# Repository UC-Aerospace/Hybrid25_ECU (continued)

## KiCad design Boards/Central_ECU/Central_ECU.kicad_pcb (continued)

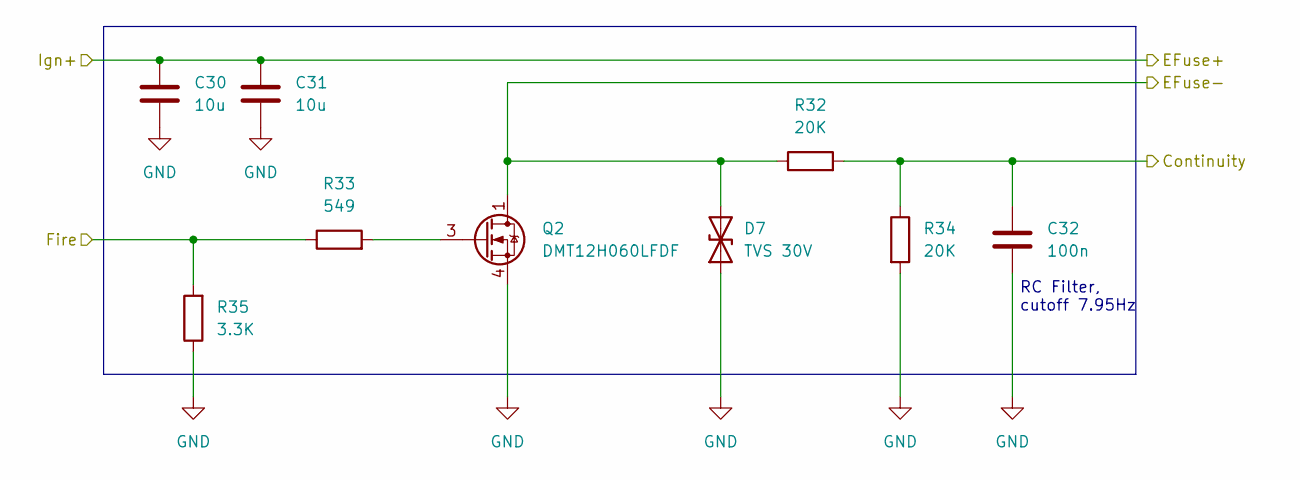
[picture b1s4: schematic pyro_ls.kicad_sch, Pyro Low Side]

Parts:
C30, C31: 10u; C_1206_3216Metric
C32: 100n; C_0603_1608Metric
D7: TVS 30V; D_SOD-882; MPN PESD1CANFD30L-QYL
Q2: DMT12H060LFDF; Diodes_UDFN2020-6_Type-F; MPN DMT12H060LFDF-7
R32, R34: 20K; R_0603_1608Metric
R33: 549; R_0603_1608Metric
R35: 3.3K; R_0603_1608Metric

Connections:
/Connectors/EMATCH_1+: C30.1, C31.1; also elsewhere on the board
/Connectors/EMATCH_2-: D7.2 (A2), Q2.1, Q2.2 (D), Q2.5 (D), Q2.6 (D), Q2.7 (D), R32.1; also elsewhere on the board
/EMATCH_2_FIRE: R33.1, R35.2; also elsewhere on the board
/Interlocked/Pyro Low Side1/Continuity: C32.1, R32.2, R34.1; also elsewhere on the board
GND: C30.2, C31.2, C32.2, D7.1 (A1), Q2.4, Q2.8 (S), R34.2, R35.1; also elsewhere on the board
unnamed: Q2.3, R33.2

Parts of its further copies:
C33, C34: 10u; C_1206_3216Metric
C35: 100n; C_0603_1608Metric
D15: TVS 30V; D_SOD-882; MPN PESD1CANFD30L-QYL
Q3: DMT12H060LFDF; Diodes_UDFN2020-6_Type-F; MPN DMT12H060LFDF-7
R36, R38: 20K; R_0603_1608Metric
R37: 549; R_0603_1608Metric
R39: 3.3K; R_0603_1608Metric

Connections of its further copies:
/Connectors/EMATCH_1+: C33.1, C34.1; also elsewhere on the board
/Connectors/EMATCH_1-: D15.2 (A2), Q3.1, Q3.2 (D), Q3.5 (D), Q3.6 (D), Q3.7 (D), R36.1; also elsewhere on the board
/EMATCH_1_FIRE: R37.1, R39.2; also elsewhere on the board
/Interlocked/Pyro Low Side/Continuity: C35.1, R36.2, R38.1; also elsewhere on the board
GND: C33.2, C34.2, C35.2, D15.1 (A1), Q3.4, Q3.8 (S), R38.2, R39.1; also elsewhere on the board
unnamed: Q3.3, R37.2

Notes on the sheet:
RC Filter, cutoff 7.95Hz

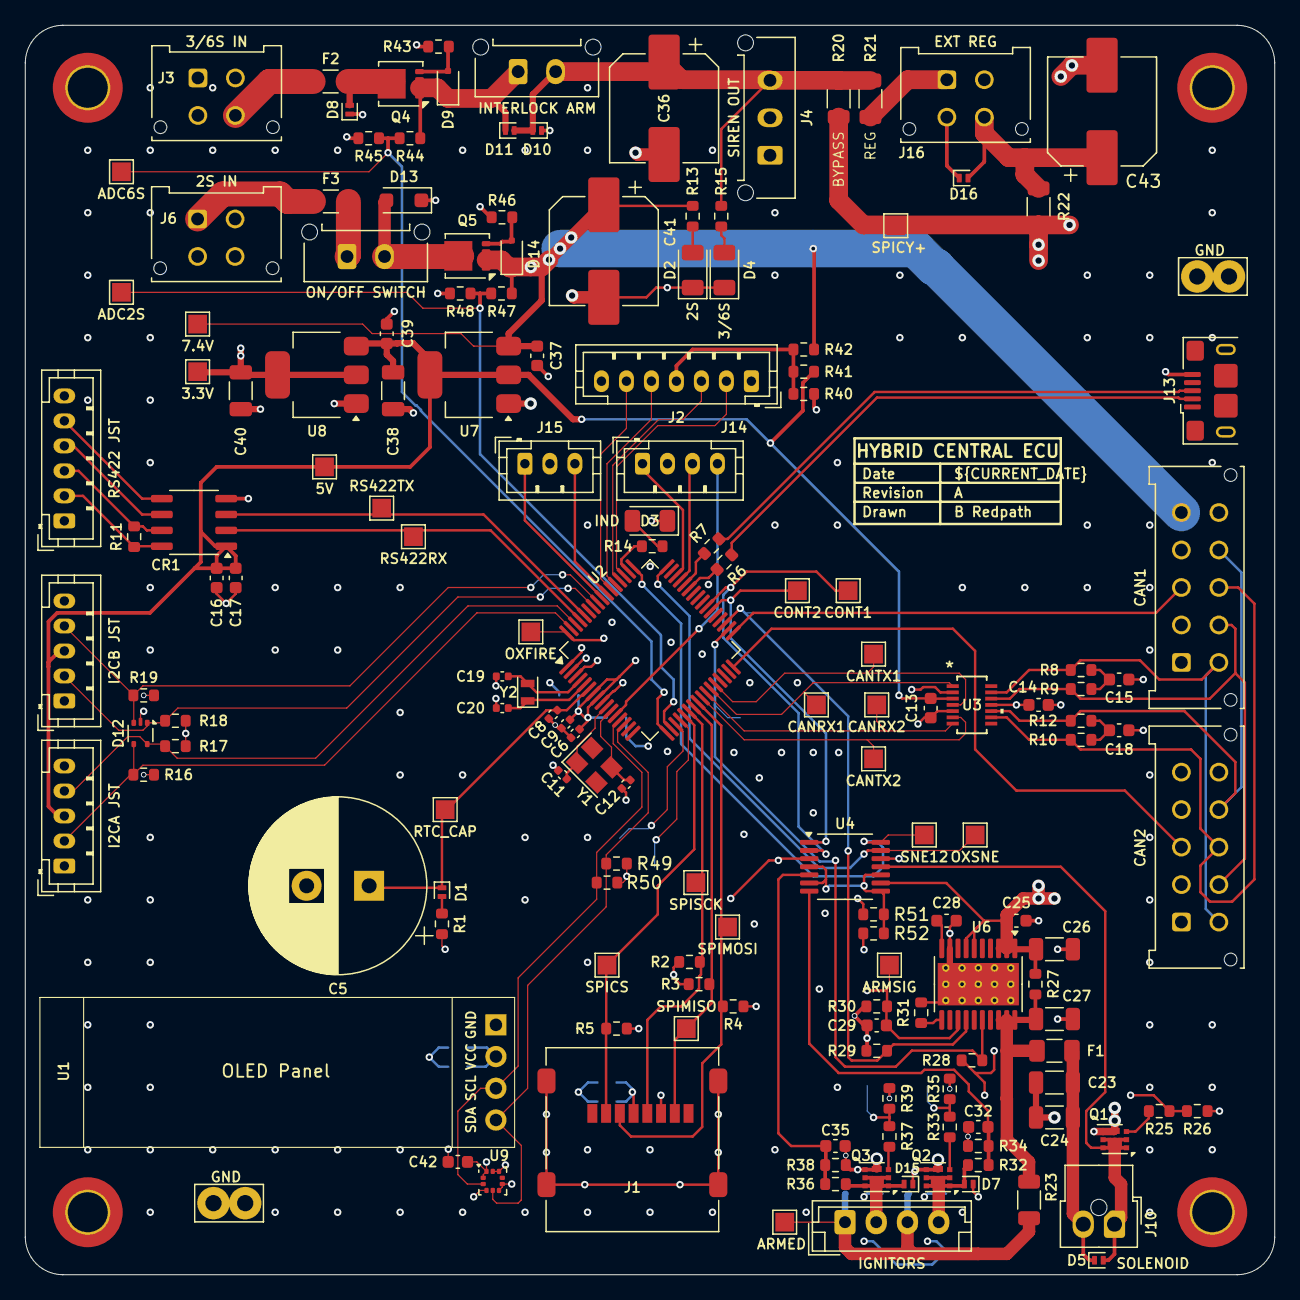
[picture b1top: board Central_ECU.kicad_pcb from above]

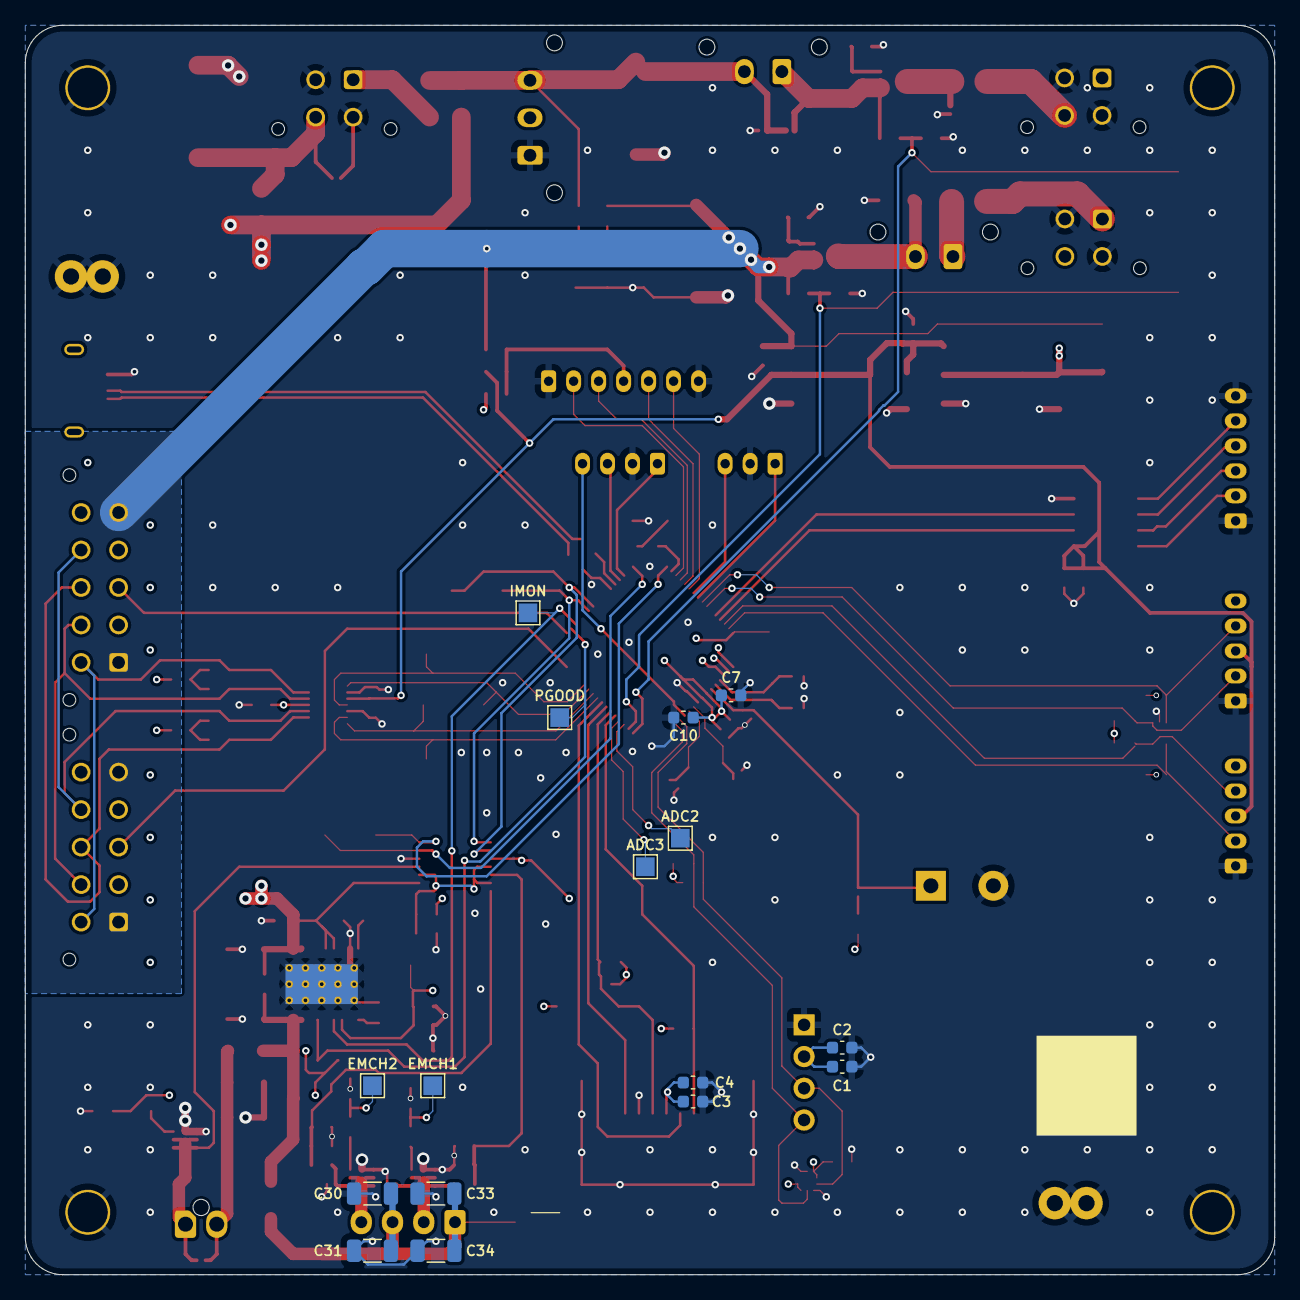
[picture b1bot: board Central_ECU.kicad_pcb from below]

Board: 4 copper layers, 100.0 x 100.0 mm, 180 parts (16 on the bottom side), 93 nets.

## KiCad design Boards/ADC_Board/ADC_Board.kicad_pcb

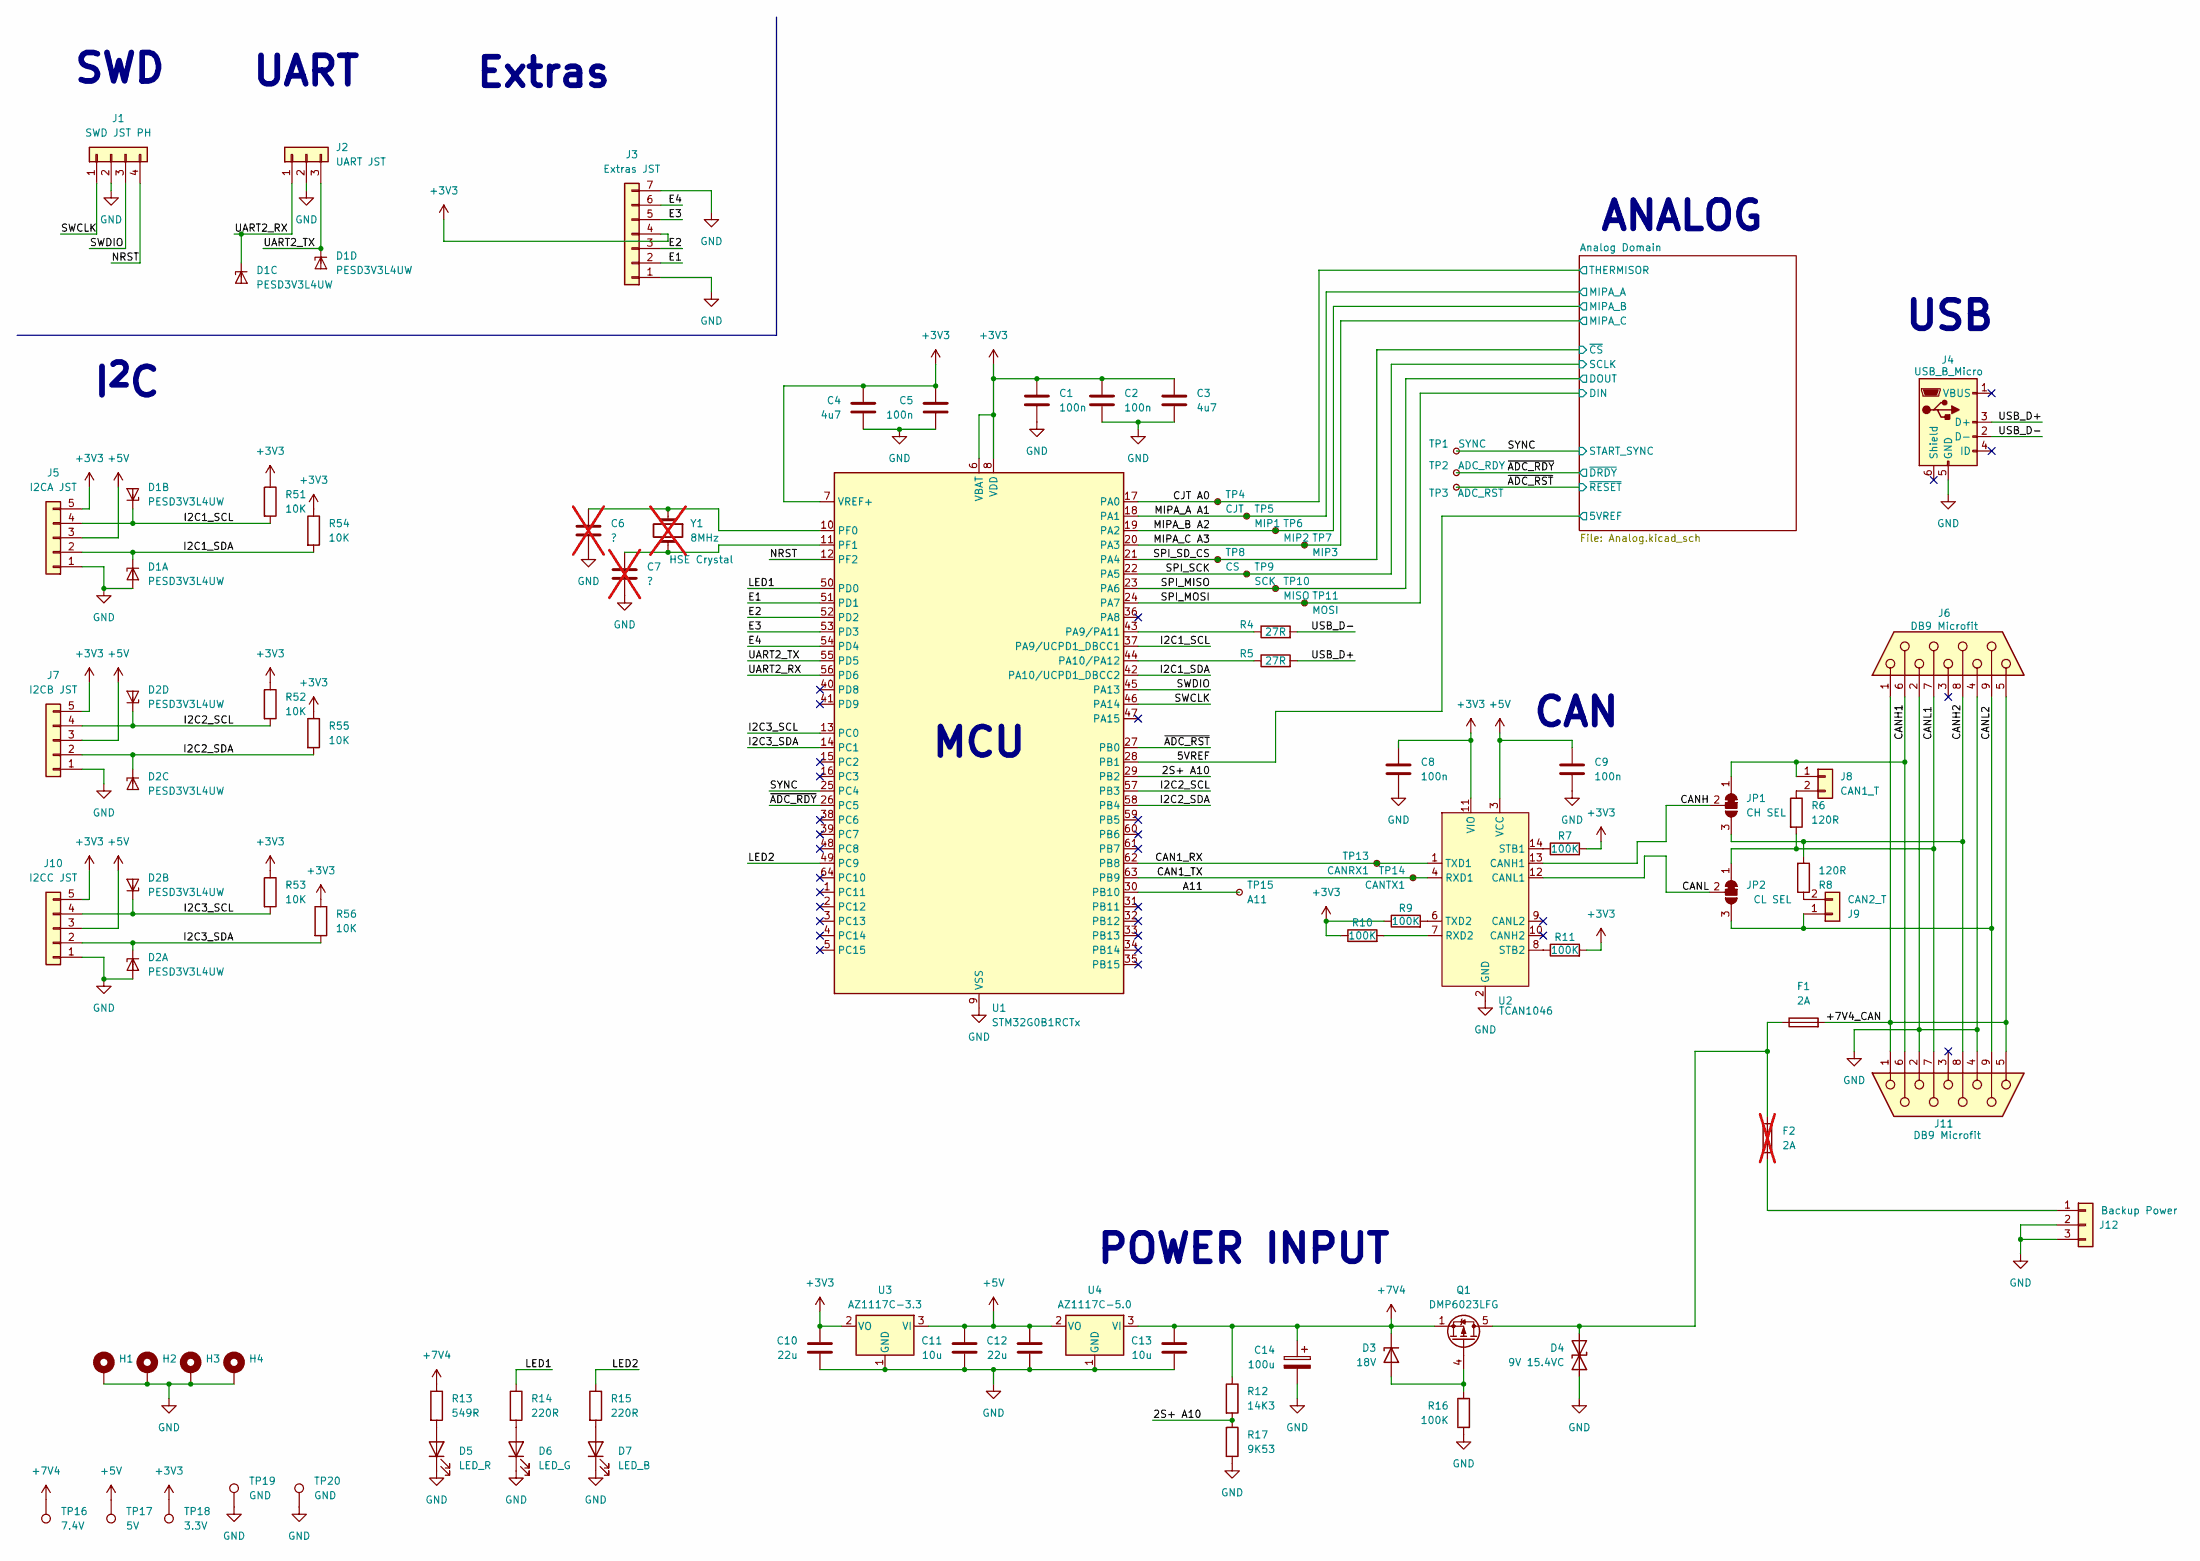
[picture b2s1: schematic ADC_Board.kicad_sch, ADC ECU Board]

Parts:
C1, C2, C5: 100n; C_0402_1005Metric
C3, C4: 4u7; C_0603_1608Metric
C6, C7: ?; C_0402_1005Metric; not fitted
C8, C9: 100n; C_0603_1608Metric
C10, C12: 22u; C_1206_3216Metric
C11, C13: 10u; C_0603_1608Metric
C14: 100u; CP_Elec_8x10.5; MPN A768KS107M1HLAE030
D1, D2: PESD3V3L4UW; SOT-665
D3: 18V; D_SOD-323F; MPN MM3Z18VB
D4: 9V 15.4VC; D_SOD-123F; MPN SMF9.0CA
D5: LED_R; LED_1206_3216Metric; MPN LTST-C150KRKT
D6: LED_G; LED_1206_3216Metric; MPN LTST-C150KGKT
D7: LED_B; LED_1206_3216Metric; MPN LTST-C150TBKT
F1: 2A; Fuse_1206_3216Metric
F2: 2A; Fuse_1206_3216Metric; not fitted
H1, H2, H3, H4: MountingHole_3.2mm_M3_DIN965_Pad_TopOnly
J1: SWD JST PH; JST_PH_B4B-PH-K_1x04_P2.00mm_Vertical; MPN B4B-PH-K-S
J2: UART JST; JST_PH_B3B-PH-K_1x03_P2.00mm_Vertical; MPN B3B-PH-K-S
J3: Extras JST; JST_PH_B7B-PH-K_1x07_P2.00mm_Vertical; MPN B7B-PH-K-S
J4: USB_B_Micro; USB_Micro-B_Amphenol_10118193-0001LF_Horizontal; MPN 10118193-0001LF
J5: I2CA JST; JST_PH_B5B-PH-K_1x05_P2.00mm_Vertical; MPN B6B-PH-K-S
J6: DB9 Microfit; DSUB-9_Pins_Horizontal_P2.77x2.84mm_EdgePinOffset7.70mm_Hou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; MPN A-DS 09 A/KG-T2S
J7: I2CB JST; JST_PH_B5B-PH-K_1x05_P2.00mm_Vertical; MPN B5B-PH-K-S
J8: CAN1_T; PinHeader_1x02_P2.54mm_Vertical
J9: CAN2_T; PinHeader_1x02_P2.54mm_Vertical
J10: I2CC JST; JST_PH_B5B-PH-K_1x05_P2.00mm_Vertical; MPN B5B-PH-K-S
J11: DB9 Microfit; DSUB-9_Pins_Horizontal_P2.77x2.84mm_EdgePinOffset7.70mm_Hou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; MPN A-DF 09 A/KG-T2S
J12: Backup Power; Molex_Micro-Fit_3.0_43650-0315_1x03_P3.00mm_Vertical; MPN 436500315
JP1: CH SEL; SolderJumper-3_P1.3mm_Bridged12_RoundedPad1.0x1.5mm
JP2: CL SEL; SolderJumper-3_P1.3mm_Bridged12_RoundedPad1.0x1.5mm
Q1: DMP6023LFG; Diodes_PowerDI3333-8; MPN DMP6023LFG-7
R4, R5: 27R; R_0603_1608Metric
R6, R8: 120R; R_0603_1608Metric
R7, R9, R10, R11, R16: 100K; R_0603_1608Metric
R12: 14K3; R_0603_1608Metric
R13: 549R; R_0603_1608Metric
R14, R15: 220R; R_0603_1608Metric
R17: 9K53; R_0603_1608Metric
R51, R52, R53, R54, R55, R56: 10K; R_0603_1608Metric
TP1: SYNC; TestPoint_Pad_D1.0mm
TP2: ADC_RDY; TestPoint_Pad_D1.0mm
TP3: ADC_RST; TestPoint_Pad_D1.0mm
TP4: CJT; TestPoint_Pad_D1.0mm
TP5: MIP1; TestPoint_Pad_D1.0mm
TP6: MIP2; TestPoint_Pad_D1.0mm
TP7: MIP3; TestPoint_Pad_D1.0mm
TP8: CS; TestPoint_Pad_D1.0mm
TP9: SCK; TestPoint_Pad_D1.0mm
TP10: MISO; TestPoint_Pad_D1.0mm
TP11: MOSI; TestPoint_Pad_D1.0mm
TP13: CANRX1; TestPoint_Pad_D1.0mm
TP14: CANTX1; TestPoint_Pad_D1.0mm
TP15: A11; TestPoint_Pad_D1.0mm
TP16: 7.4V; TestPoint_Pad_D1.0mm
TP17: 5V; TestPoint_Pad_D1.0mm
TP18: 3.3V; TestPoint_Pad_D1.0mm
TP19, TP20: GND; TestPoint_Bridge_Pitch2.54mm_Drill1.3mm
U1: STM32G0B1RCTx; LQFP-64_10x10mm_P0.5mm; MPN STM32G0B1RCT6
U2: TCAN1046; SOT23_DYY_TEX; MPN TCAN1046AVDYYRQ1
U3: AZ1117C-3.3; SOT-223-3_TabPin2; MPN AZ1117CH-3.3TRG1
U4: AZ1117C-5.0; SOT-223-3_TabPin2; MPN AZ1117CH-5.0TRG1
Y1: 8MHz; Crystal_SMD_Abracon_ABM8G-4Pin_3.2x2.5mm; not fitted

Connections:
+3V3: C1.1, C2.1, C3.1, C4.1, C5.1, C8.1, C10.1, J3.4, J5.5, J7.5, J10.5, R7.2, R9.1, R10.1, R11.2, R51.1, R52.1, R53.1, R54.1, R55.1, R56.1, TP18.1, U1.6 (VBAT), U1.7 (VREF+), U1.8 (VDD), U2.11 (VIO), U3.2 (VO); also elsewhere on the board
+5V: C9.1, C11.1, C12.1, J5.3, J7.3, J10.3, TP17.1, U2.3 (VCC), U3.3 (VI), U4.2 (VO); also elsewhere on the board
+7V4: C13.1, C14.1, D3.1 (K), Q1.1 (S), Q1.2 (S), Q1.3 (S), R12.1, R13.1, TP16.1, U4.3 (VI)
/2S+ A10: R12.2, R17.1, U1.29 (PB2)
/5VREF: U1.28 (PB1); also elsewhere on the board
/+7V4_CAN: F1.2, J6.1, J6.5, J11.1, J11.5
/A11: TP15.1, U1.30 (PB10)
/CAN1_RX: TP13.1, U1.62 (PB8), U2.1 (TXD1)
/CAN1_TX: TP14.1, U1.63 (PB9), U2.4 (RXD1)
/CANH: JP1.2 (C), U2.13 (CANH1)
/CANH1: J6.6, J8.1, J11.6, JP1.1 (A)
/CANH2: J6.8, J11.8, JP1.3 (B), R8.2
/CANL: JP2.2 (C), U2.12 (CANL1)
/CANL1: J6.7, J11.7, JP2.1 (A), R6.2
/CANL2: J6.9, J9.1, J11.9, JP2.3 (B)
/CJT A0: TP4.1, U1.17 (PA0); also elsewhere on the board
/E1: J3.2, U1.51 (PD1)
/E2: J3.3, U1.52 (PD2)
/E3: J3.5, U1.53 (PD3)
/E4: J3.6, U1.54 (PD4)
/I2C1_SCL: D1.3 (K2), J5.4, R51.2, U1.37 (PA9/UCPD1_DBCC1)
/I2C1_SDA: D1.1 (K1), J5.2, R54.2, U1.42 (PA10/UCPD1_DBCC2)
/I2C2_SCL: D2.5 (K4), J7.4, R52.2, U1.57 (PB3)
/I2C2_SDA: D2.4 (K3), J7.2, R55.2, U1.58 (PB4)
/I2C3_SCL: D2.3 (K2), J10.4, R53.2, U1.13 (PC0)
/I2C3_SDA: D2.1 (K1), J10.2, R56.2, U1.14 (PC1)
/LED1: R14.1, U1.50 (PD0)
/LED2: R15.1, U1.49 (PC9)
/MIPA_A A1: TP5.1, U1.18 (PA1); also elsewhere on the board
/MIPA_B A2: TP6.1, U1.19 (PA2); also elsewhere on the board
/MIPA_C A3: TP7.1, U1.20 (PA3); also elsewhere on the board
/NRST: J1.4, U1.12 (PF2)
/SPI_MISO: TP10.1, U1.23 (PA6); also elsewhere on the board
/SPI_MOSI: TP11.1, U1.24 (PA7); also elsewhere on the board
/SPI_SCK: TP9.1, U1.22 (PA5); also elsewhere on the board
/SPI_SD_CS: TP8.1, U1.21 (PA4); also elsewhere on the board
/SWCLK: J1.1, U1.46 (PA14)
/SWDIO: J1.3, U1.45 (PA13)
/SYNC: TP1.1, U1.25 (PC4); also elsewhere on the board
/UART2_RX: D1.4 (K3), J2.1, U1.56 (PD6)
/UART2_TX: D1.5 (K4), J2.3, U1.55 (PD5)
/USB_D+: J4.3 (D+), R5.2
/USB_D-: J4.2 (D-), R4.2
/~ADC_RDY: TP2.1, U1.26 (PC5); also elsewhere on the board
/~ADC_RST: TP3.1, U1.27 (PB0); also elsewhere on the board
GND: C1.2, C2.2, C3.2, C4.2, C5.2, C6.2, C7.2, C8.2, C9.2, C10.2, C11.2, C12.2, C13.2, C14.2, D1.2 (A), D2.2 (A), D4.1 (A1), D5.1 (K), D6.1 (K), D7.1 (K), H1.1, H2.1, H3.1, H4.1, J1.2, J2.2, J3.1, J3.7, J4.5 (GND), J5.1, J6.2, J6.4, J7.1, J10.1, J11.2, J11.4, J12.2, J12.3, R16.2, R17.2, TP19.1, TP20.1, U1.9 (VSS), U2.2 (GND), U2.5 (GND), U3.1 (GND), U4.1 (GND); also elsewhere on the board
unnamed: D3.2 (A), Q1.4 (G), R16.1
unnamed: D4.2 (A2), F1.1, F2.2, Q1.5 (D)
unnamed: D5.2 (A), R13.2
unnamed: D6.2 (A), R14.2
unnamed: D7.2 (A), R15.2
unnamed: J8.2, R6.1
unnamed: J9.2, R8.1
unnamed: F2.1, J12.1
unnamed: R4.1, U1.43 (PA9/PA11)
unnamed: R5.1, U1.44 (PA10/PA12)
unnamed: C6.1, U1.10 (PF0), Y1.1
unnamed: C7.1, U1.11 (PF1), Y1.3 (2)
unnamed: R10.2, U2.7 (RXD2)
unnamed: R7.1, U2.14 (STB1)
unnamed: R11.1, U2.8 (STB2)
unnamed: R9.2, U2.6 (TXD2)

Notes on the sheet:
ANALOG
SWD
POWER INPUT
UART
CAN
I^{2}C
Extras
USB
MCU

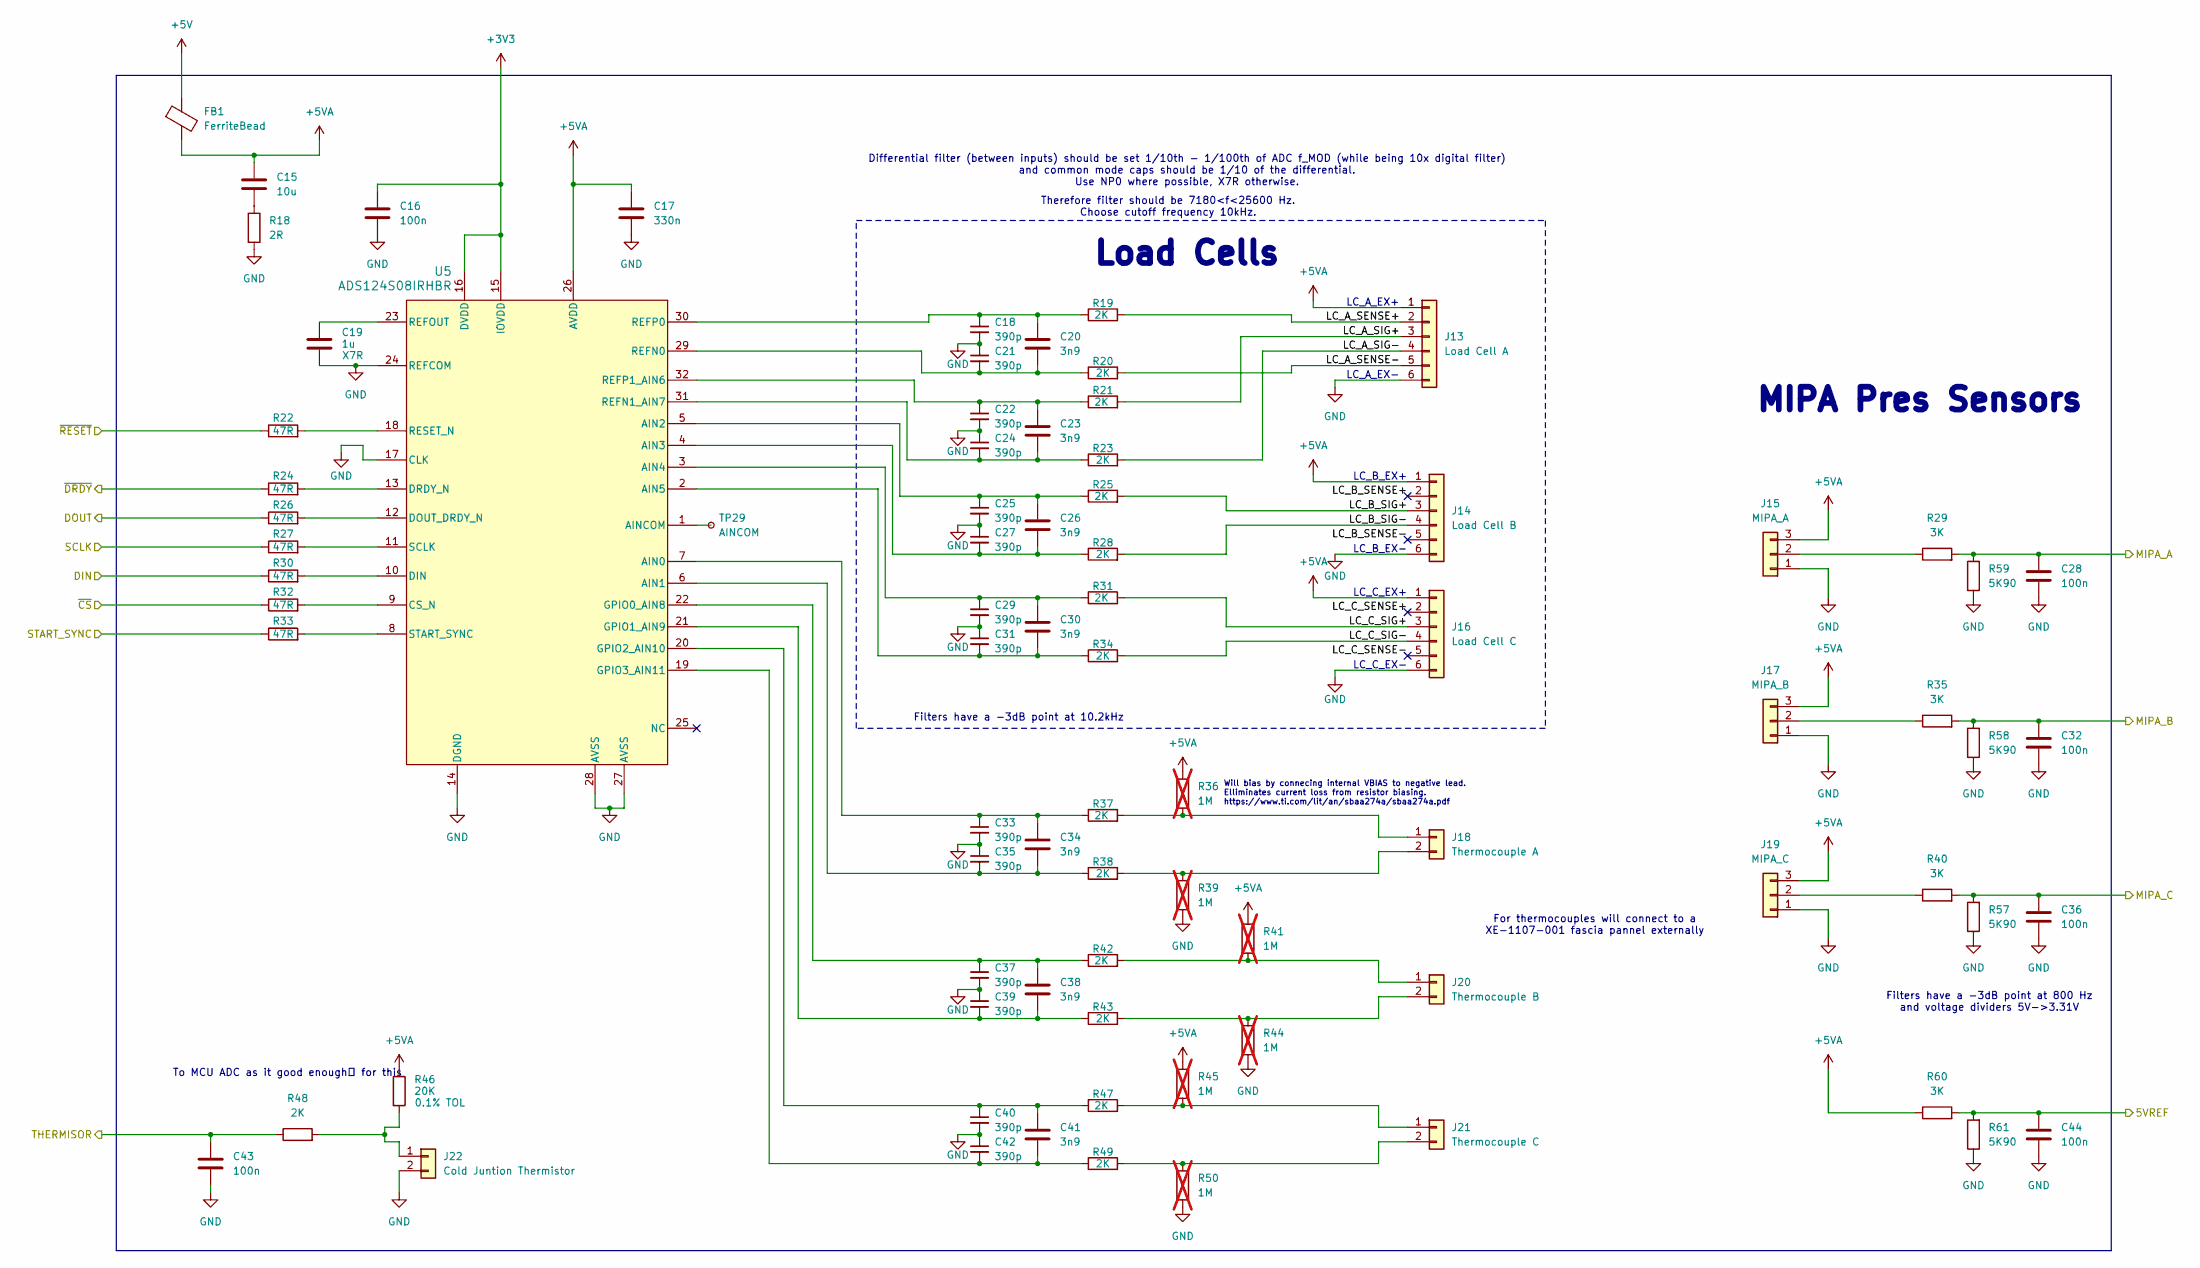
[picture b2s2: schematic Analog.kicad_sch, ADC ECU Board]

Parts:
C15: 10u; C_0603_1608Metric
C16, C28, C32, C36, C43, C44: 100n; C_0603_1608Metric
C17: 330n; C_0603_1608Metric
C18, C21, C22, C24, C25, C27, C29, C31, C33, C35, C37, C39, C40, C42: 390p; C_0402_1005Metric
C19: 1u; C_0603_1608Metric
C20, C23, C26, C30, C34, C38, C41: 3n9; C_0402_1005Metric
FB1: FerriteBead; L_1206_3216Metric; MPN BBUP00321611121Y00
J13: Load Cell A; JST_PH_B6B-PH-K_1x06_P2.00mm_Vertical
J14: Load Cell B; JST_PH_B6B-PH-K_1x06_P2.00mm_Vertical
J15: MIPA_A; JST_PH_B3B-PH-K_1x03_P2.00mm_Vertical
J16: Load Cell C; JST_PH_B6B-PH-K_1x06_P2.00mm_Vertical
J17: MIPA_B; JST_PH_B3B-PH-K_1x03_P2.00mm_Vertical
J18: Thermocouple A; JST_PH_B2B-PH-K_1x02_P2.00mm_Vertical
J19: MIPA_C; JST_PH_B3B-PH-K_1x03_P2.00mm_Vertical
J20: Thermocouple B; JST_PH_B2B-PH-K_1x02_P2.00mm_Vertical
J21: Thermocouple C; JST_PH_B2B-PH-K_1x02_P2.00mm_Vertical
J22: Cold Juntion Thermistor; JST_PH_B2B-PH-K_1x02_P2.00mm_Vertical
R18: 2R; R_0603_1608Metric
R19, R20, R21, R23, R25, R28, R31, R34, R37, R38, R42, R43, R47, R49: 2K; R_0402_1005Metric
R22, R24, R26, R27, R30, R32, R33: 47R; R_0603_1608Metric
R29, R35, R40, R60: 3K; R_0603_1608Metric
R36, R39, R41, R44, R45, R50: 1M; R_0402_1005Metric; not fitted
R46: 20K; R_0603_1608Metric
R48: 2K; R_0603_1608Metric
R57, R58, R59, R61: 5K90; R_0603_1608Metric
TP29: AINCOM; TestPoint_Pad_1.5x1.5mm
U5: ADS124S08IRHBR; QFN-32-1EP_5x5mm_P0.5mm_EP3.1x3.1mm; MPN ADS124S08IRHBR

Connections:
+3V3: C16.1, U5.15 (IOVDD), U5.16 (DVDD); also elsewhere on the board
+5V: FB1.1; also elsewhere on the board
+5VA: C15.1, C17.1, FB1.2, J13.1, J14.1, J15.3, J16.1, J17.3, J19.3, R36.1, R41.1, R45.1, R46.1, R60.1, U5.26 (AVDD)
/5VREF: C44.1, R60.2, R61.2; also elsewhere on the board
/Analog Domain/LC_A_SENSE+: J13.2, R19.2
/Analog Domain/LC_A_SENSE-: J13.5, R20.2
/Analog Domain/LC_A_SIG+: J13.3, R21.2
/Analog Domain/LC_A_SIG-: J13.4, R23.2
/Analog Domain/LC_B_SENSE+: J14.2
/Analog Domain/LC_B_SENSE-: J14.5
/Analog Domain/LC_B_SIG+: J14.3, R25.2
/Analog Domain/LC_B_SIG-: J14.4, R28.2
/Analog Domain/LC_C_SENSE+: J16.2
/Analog Domain/LC_C_SENSE-: J16.5
/Analog Domain/LC_C_SIG+: J16.3, R31.2
/Analog Domain/LC_C_SIG-: J16.4, R34.2
/CJT A0: C43.1, R48.1; also elsewhere on the board
/MIPA_A A1: C28.1, R29.2, R59.2; also elsewhere on the board
/MIPA_B A2: C32.1, R35.2, R58.2; also elsewhere on the board
/MIPA_C A3: C36.1, R40.2, R57.2; also elsewhere on the board
/SPI_MISO: R26.1; also elsewhere on the board
/SPI_MOSI: R30.1; also elsewhere on the board
/SPI_SCK: R27.1; also elsewhere on the board
/SPI_SD_CS: R32.1; also elsewhere on the board
/SYNC: R33.1; also elsewhere on the board
/~ADC_RDY: R24.1; also elsewhere on the board
/~ADC_RST: R22.1; also elsewhere on the board
GND: C16.2, C17.2, C18.2, C19.2, C21.1, C22.2, C24.1, C25.2, C27.1, C28.2, C29.2, C31.1, C32.2, C33.2, C35.1, C36.2, C37.2, C39.1, C40.2, C42.1, C43.2, C44.2, J13.6, J14.6, J15.1, J16.6, J17.1, J19.1, J22.2, R18.2, R39.2, R44.2, R50.2, R57.1, R58.1, R59.1, R61.1, U5.14 (DGND), U5.17 (CLK), U5.24 (REFCOM), U5.27 (AVSS), U5.28 (AVSS), U5.33 (PAD); also elsewhere on the board
unnamed: C15.2, R18.1
unnamed: J15.2, R29.1
unnamed: J17.2, R35.1
unnamed: J18.1, R36.2, R37.2
unnamed: J18.2, R38.2, R39.1
unnamed: J19.2, R40.1
unnamed: J20.1, R41.2, R42.2
unnamed: J20.2, R43.2, R44.1
unnamed: J21.1, R45.2, R47.2
unnamed: J21.2, R49.2, R50.1
unnamed: J22.1, R46.2, R48.2
unnamed: C33.1, C34.1, R37.1, U5.7 (AIN0)
unnamed: C34.2, C35.2, R38.1, U5.6 (AIN1)
unnamed: C25.1, C26.1, R25.1, U5.5 (AIN2)
unnamed: C26.2, C27.2, R28.1, U5.4 (AIN3)
unnamed: C29.1, C30.1, R31.1, U5.3 (AIN4)
unnamed: C30.2, C31.2, R34.1, U5.2 (AIN5)
unnamed: TP29.1, U5.1 (AINCOM)
unnamed: R32.2, U5.9 (CS_N)
unnamed: R30.2, U5.10 (DIN)
unnamed: R26.2, U5.12 (DOUT_DRDY_N)
unnamed: R24.2, U5.13 (DRDY_N)
unnamed: C37.1, C38.1, R42.1, U5.22 (GPIO0_AIN8)
unnamed: C38.2, C39.2, R43.1, U5.21 (GPIO1_AIN9)
unnamed: C40.1, C41.1, R47.1, U5.20 (GPIO2_AIN10)
unnamed: C41.2, C42.2, R49.1, U5.19 (GPIO3_AIN11)
unnamed: C20.2, C21.2, R20.1, U5.29 (REFN0)
unnamed: C23.2, C24.2, R23.1, U5.31 (REFN1_AIN7)
unnamed: C19.1, U5.23 (REFOUT)
unnamed: C18.1, C20.1, R19.1, U5.30 (REFP0)
unnamed: C22.1, C23.1, R21.1, U5.32 (REFP1_AIN6)
unnamed: R22.2, U5.18 (RESET_N)
unnamed: R27.2, U5.11 (SCLK)
unnamed: R33.2, U5.8 (START_SYNC)

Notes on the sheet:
Differential filter (between inputs) should be set 1/10th - 1/100th of ADC f_MOD (while being 10x digital filter) and common mode caps should be 1/10 of the differential. Use NP0 where possible, X7R otherwise.
Load Cells
LC_B_EX-
LC_C_EX-
To MCU ADC as it good enough™ for this
MIPA Pres Sensors
Therefore filter should be 7180<f<25600 Hz. Choose cutoff frequency 10kHz.
LC_A_EX+
LC_B_EX+
Filters have a -3dB point at 10.2kHz
LC_C_EX+
LC_A_EX-
Filters have a -3dB point at 800 Hz and voltage dividers 5V->3.31V
For thermocouples will connect to a XE-1107-001 fascia pannel externally
Will bias by connecing internal VBIAS to negative lead. Elliminates current loss from resistor biasing. https://www.ti.com/lit/an/sbaa274a/sbaa274a.pdf

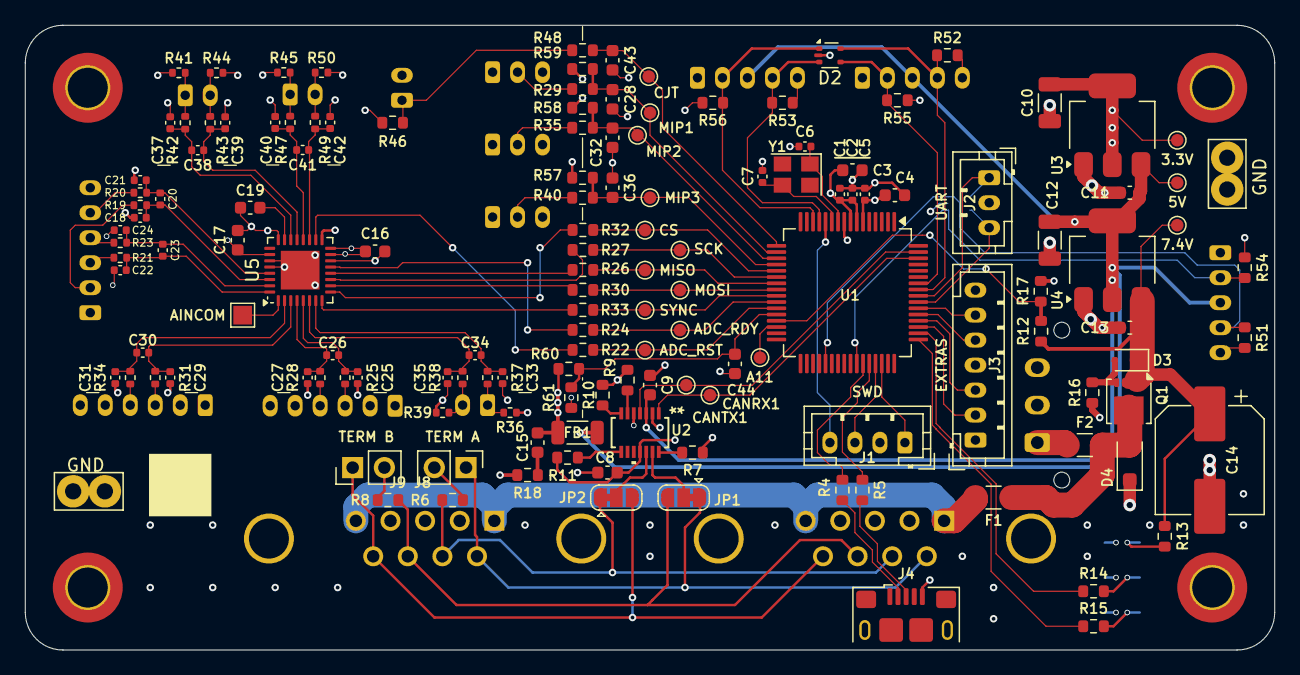
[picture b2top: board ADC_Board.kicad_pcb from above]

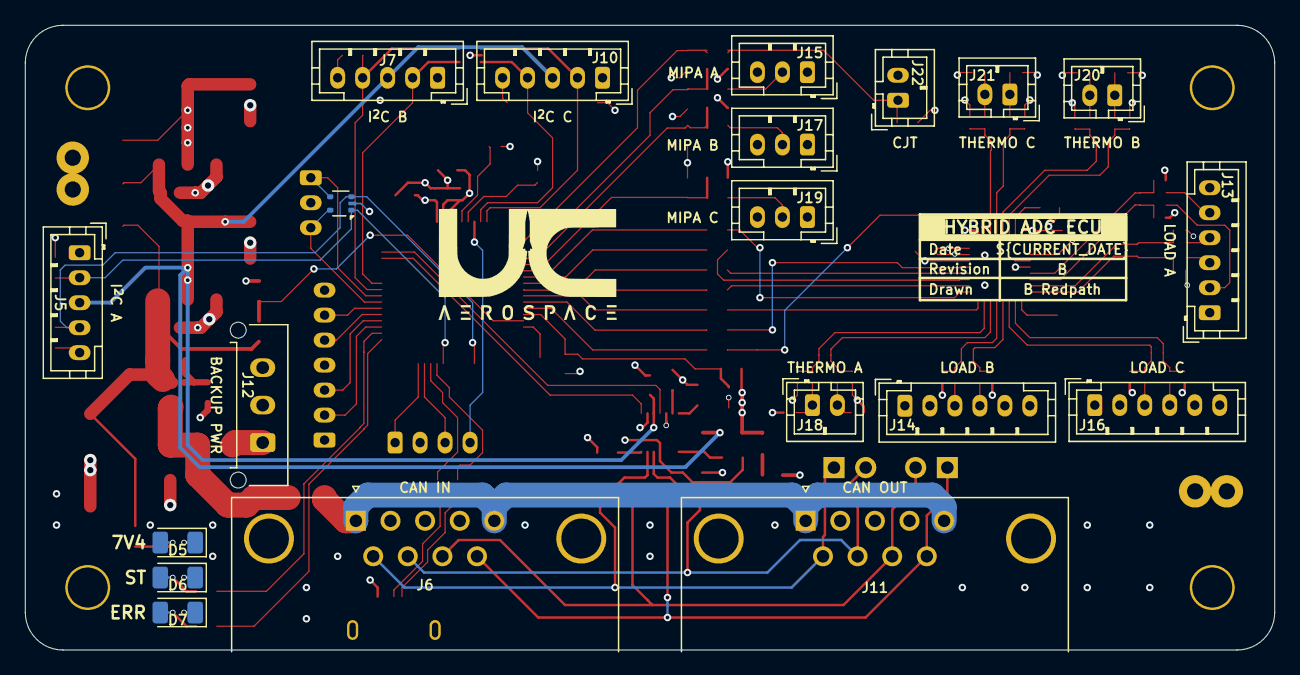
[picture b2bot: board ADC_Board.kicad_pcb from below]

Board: 4 copper layers, 100.0 x 50.0 mm, 167 parts (20 on the bottom side), 105 nets.
